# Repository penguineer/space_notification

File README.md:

netz39_space_notification
=========================

Teilprojekte der Space Notification, z.B.

  * Ansteuerung Außenlampe
  * Ampel
  * Twitter-Notification

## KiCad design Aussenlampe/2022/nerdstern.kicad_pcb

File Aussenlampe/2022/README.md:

# Nerdstern control - v2 (2022)

This PCB contains a 12V solid-state-relais to control 230V nerdstern (outdoor lamp).
A blue LED lights up when the relais is activated.

## Requirements for v2.0

* 12V SSR with zero crossing
* 2x 3-pin connectors for 230V (N, L and PE)
* Molex 2-pin PicoBlade for 12V input
* blue status LED wired to 12V

## Known issues in v2.0
* the ground plane connected to PE should exclude the 12V relais area
    * separate copper plane on existing board to a distance of at least 5mm

## Pictures (v2.0)

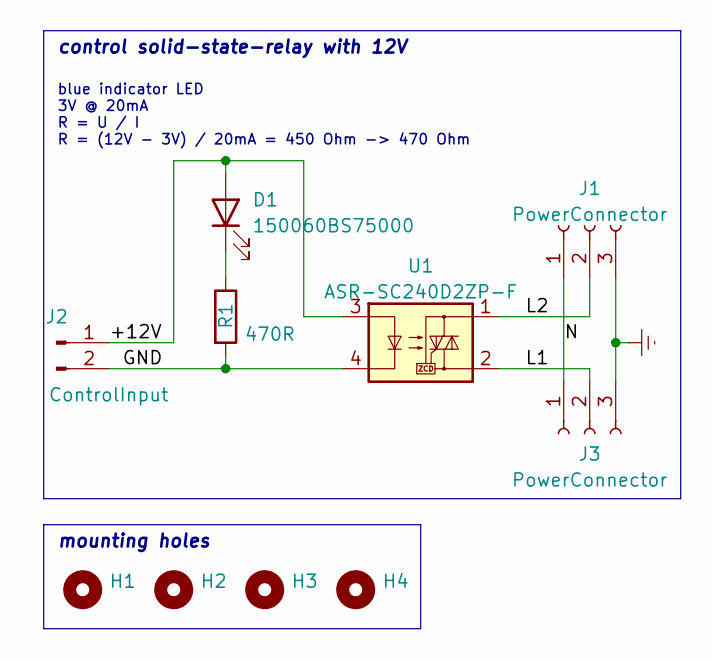
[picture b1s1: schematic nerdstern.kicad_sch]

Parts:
D1: 150060BS75000; LED_0603_1608Metric
H1, H2, H3, H4: MountingHole; MountingHole_3.2mm_M3_ISO14580
J1, J3: PowerConnector; PhoenixContact_MSTBA_2,5_3-G-5,08_1x03_P5.08mm_Horizontal
J2: ControlInput; Molex_PicoBlade_53047-0210_1x02_P1.25mm_Vertical
R1: 470R; R_0603_1608Metric
U1: ASR-SC240D2ZP-F; T-Type SSR

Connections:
/+12V: D1.2 (A), J2.1, U1.3
/GND: J2.2, R1.2, U1.4
/L1: J3.2, U1.2
/L2: J1.2, U1.1
/N: J1.1, J3.1
Earth: J1.3, J3.3
unnamed: D1.1 (K), R1.1

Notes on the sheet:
control solid-state-relay with 12V
mounting holes
blue indicator LED 3V @ 20mA R = U / I R = (12V - 3V) / 20mA = 450 Ohm -> 470 Ohm

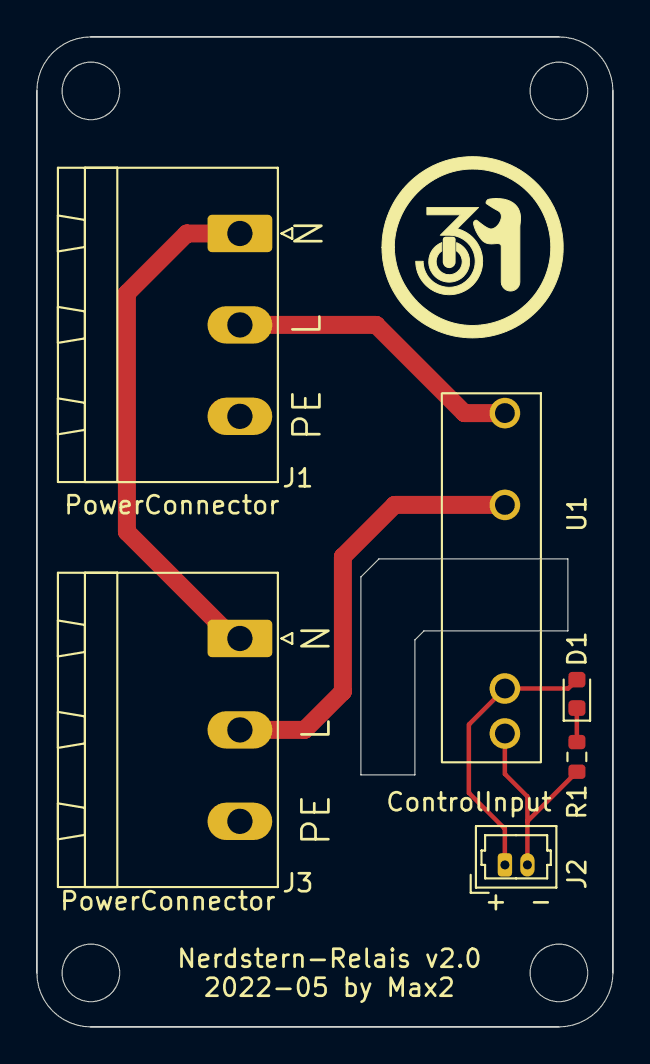
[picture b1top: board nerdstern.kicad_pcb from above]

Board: 2 copper layers, 32.0 x 55.0 mm, 10 parts (0 on the bottom side), 7 nets.

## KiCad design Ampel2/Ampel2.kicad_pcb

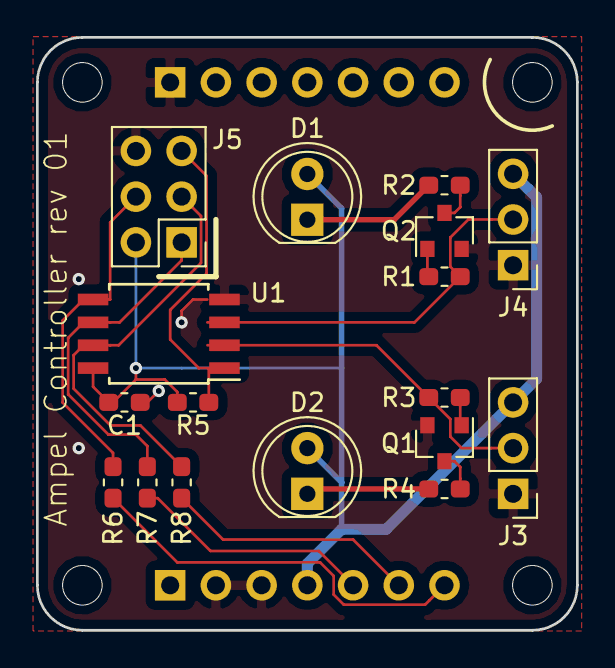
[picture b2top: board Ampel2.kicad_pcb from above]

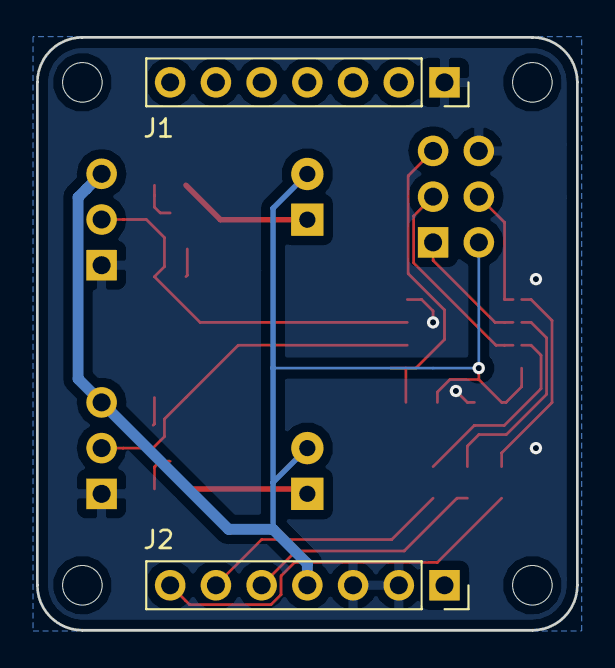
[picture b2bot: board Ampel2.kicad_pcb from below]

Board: 2 copper layers, 30.0 x 32.9 mm, 23 parts (2 on the bottom side), 17 nets.

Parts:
C1: 100n; C_0603_1608Metric_Pad1.05x0.95mm_HandSolder
D1: rd; LED_D5.0mm
D2: gn; LED_D5.0mm
J1, J2: Conn_01x07_Male; PinSocket_1x07_P2.54mm_Vertical
J3, J4: Conn_01x03_Male; PinHeader_1x03_P2.54mm_Vertical
J5: AVR-ISP-6; PinHeader_2x03_P2.54mm_Vertical
MK1, MK2, MK3, MK4: 2.0; MountingHole_2.2mm_M2_DIN965
Q1, Q2: BC 818-25; SOT-23
R1, R3: 330R; R_0603_1608Metric_Pad1.05x0.95mm_HandSolder
R2, R4: 100R; R_0603_1608Metric_Pad1.05x0.95mm_HandSolder
R5: 10K; R_0603_1608Metric_Pad1.05x0.95mm_HandSolder
R6, R7, R8: 10R; R_0603_1608Metric_Pad1.05x0.95mm_HandSolder
U1: ATtiny85V-10SU; SOIJ-8_5.3x5.3mm_P1.27mm

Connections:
+5V: C1.1, D1.2, D2.2, J2.4, J3.3, J4.3, J5.2, R5.1, U1.8
EXT_GN: J3.2, R3.2, U1.2
EXT_RD: J4.2, R1.2, U1.3
GND: C1.2, J1.1, J2.2, J2.3, J3.1, J4.1, J5.6, Q1.2, Q2.2, U1.4
INT_5V: J2.5, R7.1
ISP_MISO: J5.1, R7.2, U1.6
ISP_MOSI: J5.4, R6.2, U1.5
ISP_RST: J5.5, R5.2, U1.1
ISP_SCK: J5.3, R8.2, U1.7
unnamed: D1.1, R2.1
unnamed: D2.1, R4.1
unnamed: Q1.1, R3.1
unnamed: Q1.3, R4.2
unnamed: Q2.1, R1.1
unnamed: Q2.3, R2.2
SCL_5V: J2.6, R8.1
SDA_5V: J2.7, R6.1

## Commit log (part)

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2013-02-10 Beschreibung Teilprojekte
2013-02-10 Teilprojekte Ampel, Aussenlampe; README-Files
2013-02-11 Scan des Schaltungsentwurfs, mit einer Grobskizze für das Leiterplattenlayout
2013-02-13 Stückliste für die Steuerung der Außenlampe
2013-02-21 schematic and board layout done, routing missing
2013-02-21 Update Stückliste
2013-02-21 Entwurf Stückliste
2013-02-21 Kopie Schaltplan aus http://www.mikrocontroller.net/articles/Konstantstromquelle_fuer_Power_LED
2013-02-21 Datenblatt Schaltregler
2013-02-22 add optocopler, wirin still questionable
2013-02-28 routing and some repositioning of parts
2013-02-28 .pdf for penguineer
2013-02-28 schaltplan korrigiert
2013-03-01 routing
2013-03-01 add cc-license on board
2013-03-02 modify writing on board
2013-03-13 Eagle-Libraries für das Board
2013-03-13 Schaltplan und Board LED-Treiber
2013-03-14 Kleine Anpassung routing für mehr Massefläche
2013-03-14 add git ignore list with automatically created eagle backup files
2013-03-14 Pad-Größen und Leiterbahnbreiten angepasst
2013-03-14 Noch ein wenig Layout-Tuning in der LED-Treiberschaltung
2013-03-14 R_SENSE angepasst
2013-03-14 Schaltung nochmal angepasst
2013-03-14 entwurf controller
2013-03-15 spannungsregler
2013-03-15 some routing
2013-03-15 Jumper für Stromversorgung und Spannungsregler angepasst
2013-03-15 Schaltung und Board Spannungsversorgung
2013-03-15 Ladekondensatoren angepasst
2013-03-15 Controller und Treiber für die Ampel in verschiedene Verzeichnisse gelegt
2013-03-16 Erste Version Firmware: rot/grün-Schaltung über INPUT
2013-03-16 .gitignore für firmware-files
2013-03-16 überflüssigen Code entfernt
2013-03-16 Doku Anschlussbelegung Ampel
2013-03-16 Readme wieder ins Ampel-Verzeichnis
2013-03-16 Erweiterung Firmware: blinken
2013-03-17 Stecker angepasst
2013-03-27 Space-API-Script
2013-03-28 SpaceAPI-Sachen in eigenem Verzeichnis
2013-03-28 Neuer (provisorischer) Schildentwurf
2013-04-03 Howto SpaceStatus v1
2013-04-03 Howto SpaceStatus v2
2013-04-14 Added a TWI library and TWI control support.
2013-04-15 Code makeover in firmware: comments, added TODOs, some minor code additions and move-arounds
2013-04-16 I²C-Kommandos, tests pending
2013-04-20 Operator-Precendence fixed
2013-04-20 gitignore angepasst für twi-lib object file
2013-04-20 kleine Anpassungen
2013-04-20 Redesign des Controller-Boards auf I2C
2013-04-20 Anpassung an Anschluss vom I2C-Adapter
2013-04-20 I2C-Adapter
2013-04-20 letzte Anpassungen zum Ätzen
2013-04-22 Redesign (INT-Leitung und breitere Leitung für Spannungsversorgung)
2013-04-24 Adapter: stecker angepasst Controller: board redesign
2013-05-05 Gehäuse für den Ampelcontroller
2013-05-05 trove für den i2c-adapter
2013-05-05 Gehäusedesign v2
2013-05-05 Kleine Anpassungen im SCAD-Script
2013-05-05 trove Ampel-Controller v2
2013-05-05 trove v3
2013-05-06 modified .gitignore
2013-05-06 rm nerdstern.pdf
2013-05-06 anpassung an i2c-board
2013-05-06 kräftigeres Gehäuse und Snapper
2013-05-08 Angepasstes Trove für den Controller
2013-10-14 new buttons
    font und farben in absprache mit eriu
2013-10-14 let inkscape save its stuff
2013-10-14 adapt colors and export smaller png
2013-10-15 make logo a little smaller
2013-10-24 pending changes
2014-01-03 i3c-handling
2014-01-03 spaceapi-Script ausführbar gemacht
2014-01-03 Controller-Trove: fine-tuning für Controller-Board Anpassung Build-Umgebung
2014-01-03 aktuelle Ampel-Files
2014-02-26 remove unneeded files
2014-02-26 ReadMe für Ampel-Adapter
2014-02-26 I²C-Adapter ist nun in https://github.com/netz39/i2cbridge
2014-05-19 Check for space status before tweeting
2014-05-19 Fixed the Space API query location (actually: do the query before the change! :oops: )
2014-05-22 Changed I2C to the I3C protocol to gain compatibility with other devices and the xmppsc.
2014-05-22 Fixed some data types.
2014-05-23 Changed the programmer
2014-07-04 Schalter: Schematics für Schalter-Controller (adaptiert vom Ampel-Controller)
2014-07-13 Schalter: Ladekondensator eingefügt
2014-07-13 Schalter: Board dimensions
2014-07-13 Schalter: USI-TWI-Lib
2014-07-13 Schalter: Firmware
2014-10-10 Spacetime-Schalter nutzt nun doch attiny85
2014-10-10 Spacetime-Schalter: Halterung für Controller mit Wandabstandshalter
2014-10-10 Spacetime-Schalter: Halterung für Buchse mit Wandabstandshalter
2014-10-17 Schalter: Grundplatte, Freecad-Version
2014-10-17 Schalter: Korrigiertes DXF der Grundplatte
    (FreeCad hat iwie Probleme mit der Richtung von Kreisbögen; mit LibreCad korrigiert.)
2014-10-18 Schalter: Added fuse target to Makefile
2014-10-18 Schalter: Bugfixes in the firmware
2014-10-18 Schalter: Switch-Ports getauscht, ist in der Hardware jetzt doch anders herum verlötet.
2014-10-18 Schalter: Fix für #4
    *hust* :oops:
2014-10-18 color.sh mit i3c-Client-Aufrufen
2014-10-18 Provisorisches™ Script für SpaceStatus-Steuerung über den Schalter
2014-10-22 Schalter: Daten von der Fräse
2016-08-08 Adapt statusswitch to ipv6
2016-08-09 MQTT: Pass 1 - Switch Lights pased on SpaceAPI and Door
2017-02-04 Refine the countdown condition
2017-02-04 MQTT Pass 2 - publish lever state to topic
    See http://www.netz39.de/wiki/projects:2014:gatekeeper:mqtt#topic
    Relevant topics are
    Netz39/Things
    StatusSwitch
    Lever
    State ("open", "closed", "neutral")
2019-01-01 New Ampel controller, first draft
2019-01-06 Fix dimensions
2019-01-06 Outline and mounting holes
2019-01-13 Move upper LED
2019-01-25 Fix Attiny85 footprint
    Change to the attiny we actually have (Attiny85V-10 SU)
2019-03-23 Adapt Makefile for attiny85 and add fuse setting
2019-03-23 Adapt firmware to new LED behaviour
2019-05-05 Add python script to update SpaceAPI with added functionality (door status). The script subscribes to the revelant MQTT topics and pushes updates on new messages. Requirements: Python 3, paho-mqtt pa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
2019-05-12 add beautiful argparse command line interface
2019-05-17 add picture symlink creation & bugfix
2019-05-24 split into two image paths
2019-05-24 remove unnecessary print
2019-05-30 Move spaceapi script to non-www directory
2019-05-30 Adapt standard locations
2019-10-19 spaceapi: template: Minor corrections
    * Add root resource to website URL
    * Twitter handle is lower case
    * Add newline to end of file (jq does that and my editor as well)
2019-10-19 spaceapi: template: Replace "irc" with "jabber"
    Our IRC channel is more or less dead, we use XMPP MUC for a while now.
    This is consistent with what we announce on our website:
    http://www.netz39.de/verein/kommunikation/
2019-10-19 spaceapi: template: Add website feeds
    Add our blog and calendar feeds.
2020-12-08 Disable tweet action
2020-12-08 Add a sign for status "occupied"
2020-12-08 Link to "occupied" instead of "open"
2020-12-08 Export occupied.svg to PNG
2020-12-08 Set open-logo to "occupied" in JSON template
2020-12-08 Make occupied sign available to status
2020-12-08 SpaceAPI: Improve spacing for occupied banner
    This has the same margins as the 'closed' banner now.
2020-12-13 Use more recent usitwislave library
2021-11-07 Start processing I2C data after first byte
    RPi2 stopped sending stop conditions between frames of an I2C request
    (repeated start), which means this library does not detect the step
    between sending data and expecting a processed result.
    As we only ever send one byte of data, it is safe for now to process the
    buffer after the first byte to have the result ready when it is expected.
2022-09-27 Switch to HTTPS
2022-09-27 Change icon for "open" state from occupied to open
2022-09-28 :alien: SpaceApi: Change URL to avoid redirect
    Our wiki has moved into a container and to another URL. HTTP requests to
    the old URL are answered with a status code 301 (Moved Permanently).
    To avoid that extra request, point directly to the new URL.
2022-12-08 Move nerdstern EAGLE files to own folder
2022-12-08 Add new schematic/pcb to control Nerdstern with SSR
2022-12-09 Add ReadMe to Nerdstern v2 (2022)
2024-11-01 Fix subscription topics for door and space status lever
2024-11-02 Revamp ledcontrol to control the LEDs from MQTT topic
2024-11-02 Apply RPi2 I2C communication fix for switch
    Apply the fix from https://github.com/netz39/space_notification/pull/12
    to the switch firmware.
2024-11-02 remove spaceapi folder after move to Netz39AmpelController and Netz39SpaceAPI-Service
